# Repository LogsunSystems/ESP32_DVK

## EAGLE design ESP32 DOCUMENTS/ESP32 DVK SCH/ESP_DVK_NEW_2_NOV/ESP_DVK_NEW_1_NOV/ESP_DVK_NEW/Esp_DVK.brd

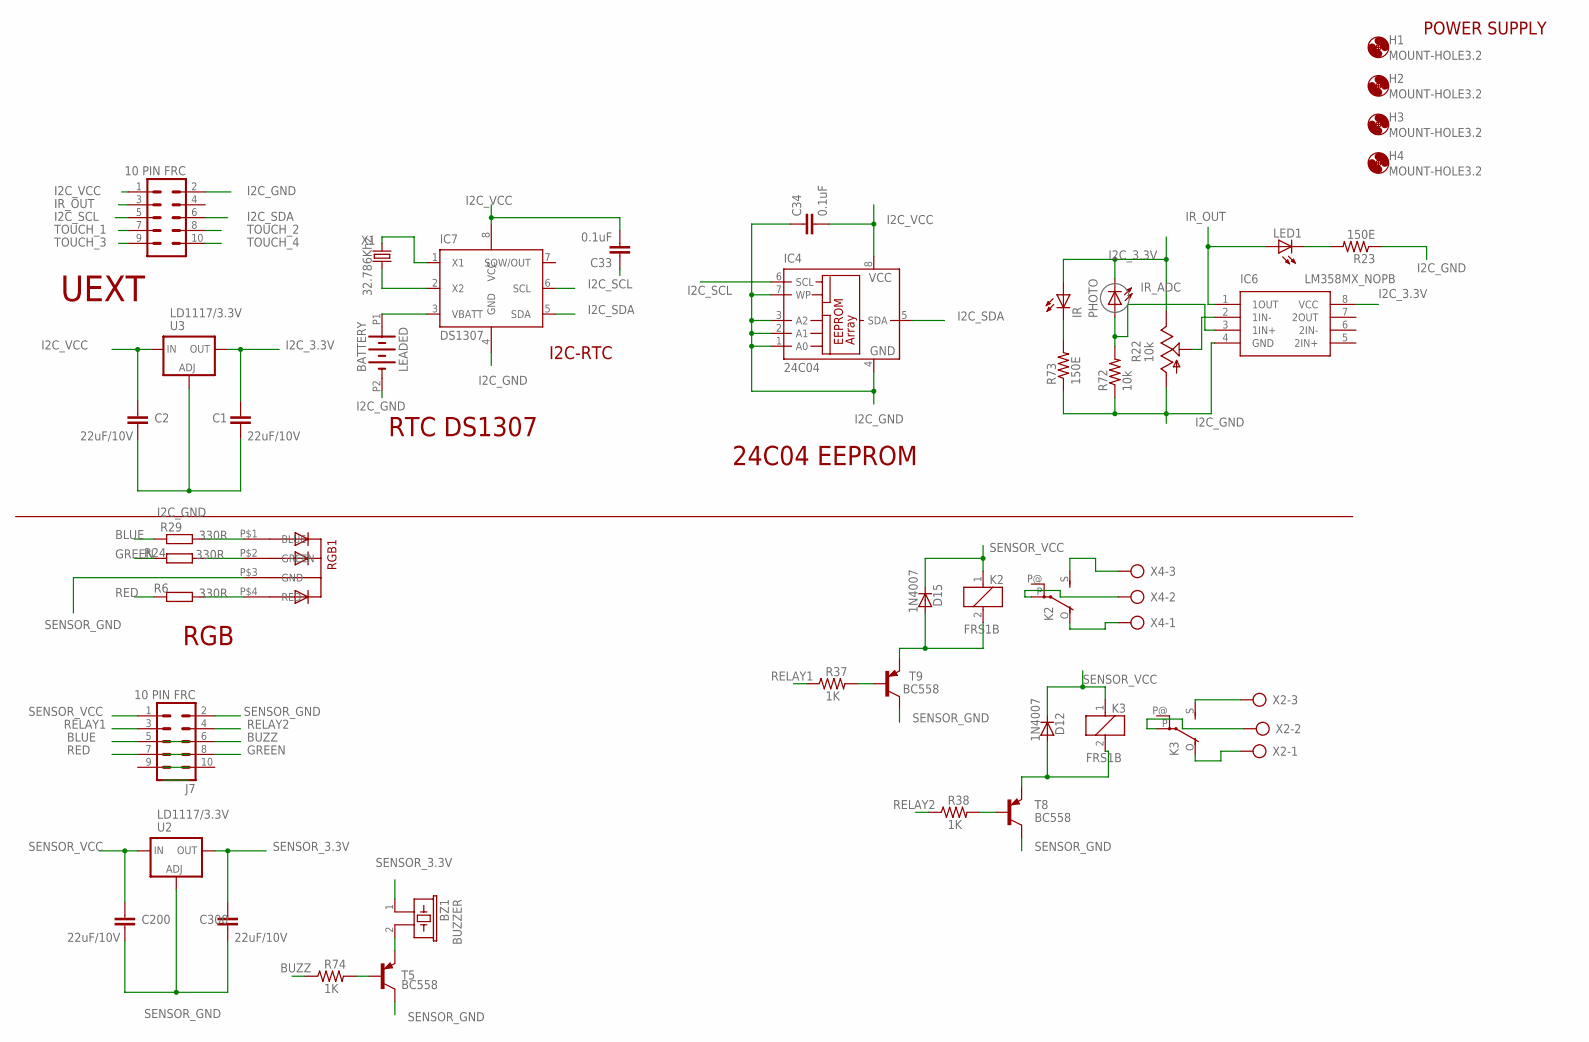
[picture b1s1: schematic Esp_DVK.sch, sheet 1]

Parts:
BATTERY: LEADED
BZ1: BUZZER; BUZZ
C1, C2, C200, C300: 22uF/10V; C1206
C33, C34: 0.1uF; C1206
D12, D15: 1N4007; MLL34
H1, H2, H3, H4: MOUNT-HOLE3.2; 3,2
IC4: 24C04; SO-08M
IC6: LM358MX_NOPB; SOIC127P600X175-8N
IC7: DS1307; SO08
IR: LED5MM
J3, J7: 10 PIN FRC; ML10
K2, K3: FRS1B
LED1: LEDCHIPLED_1206; CHIPLED_1206
PHOTO: LED5MM
R6, R24, R29: 330R; R1206
R22: 10k; RJ9W
R23, R73: 150E; R1206
R37, R38, R74: 1K; R1206@1
R72: 10k; R1206
RGB1: 5MMRGBLED; LED5MMRGB
T5, T8, T9: BC558; SOT23-EBC
U2, U3: LD1117/3.3V; SOT223
X1: 32.786Khz; TC38H
X2, X4: AK300/3

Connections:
BLUE: J7.5, R29.1
BUZZ: J7.6, R74.1
GREEN: J7.8, R24.1
I2C_3.3V: C1.2, IC6.8 (VCC), IR.A, PHOTO.K (C), R22.E, U3.4 (OUT)
I2C_GND: BATTERY.P2 (-), C1.1, C2.1, C33.1, C34.1, IC4.1 (A0), IC4.2 (A1), IC4.3 (A2), IC4.4 (GND), IC4.7 (WP), IC6.4 (GND), IC7.4 (GND), J3.2, R22.A, R23.1, R72.1, R73.1, U3.1 (ADJ)
I2C_SCL: IC4.6 (SCL), IC7.6 (SCL), J3.5
I2C_SDA: IC4.5 (SDA), IC7.5 (SDA), J3.6
I2C_VCC: C2.2, C33.2, C34.2, IC4.8 (VCC), IC7.8 (VCC), J3.1, U3.3 (IN)
IR_ADC: IC6.3 (1IN+), PHOTO.A, R72.2
IR_OUT: IC6.1 (1OUT), J3.3, LED1.A
unnamed: R24.2, RGB1.P$2 (GREEN)
unnamed: IC6.2 (1IN-), R22.S
unnamed: K3.S, X2.3
unnamed: K2.S, X4.3
unnamed: K2.P, X4.2
unnamed: R29.2, RGB1.P$1 (BLUE)
unnamed: K2.O, X4.1
unnamed: R38.2, T8.B
unnamed: IR.K (C), R73.2
unnamed: R6.2, RGB1.P$4 (RED)
unnamed: LED1.C, R23.2
unnamed: D12.A, K3.2, T8.E
unnamed: K3.P, X2.2
unnamed: K3.O, X2.1
unnamed: IC7.2 (X2), X1.1
unnamed: BATTERY.P1 (+), IC7.3 (VBATT)
unnamed: IC7.1 (X1), X1.2
unnamed: R74.2, T5.B
unnamed: BZ1.2, T5.E
unnamed: R37.2, T9.B
unnamed: D15.A, K2.2, T9.E
RED: J7.7, R6.1
RELAY1: J7.3, R37.1
RELAY2: J7.4, R38.1
SENSOR_3.3V: BZ1.1, C300.2, U2.4 (OUT)
SENSOR_GND: C200.1, C300.1, J7.2, RGB1.P$3 (GND), T5.C, T8.C, T9.C, U2.1 (ADJ)
SENSOR_VCC: C200.2, D12.C, D15.C, J7.1, K2.1, K3.1, U2.3 (IN)
SQW/OUT: IC7.7 (SQW/OUT)
TOUCH_1: J3.7
TOUCH_2: J3.8
TOUCH_3: J3.9
TOUCH_4: J3.10

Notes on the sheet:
POWER SUPPLY
I2C-RTC
RTC DS1307
24C04 EEPROM
UEXT
RGB

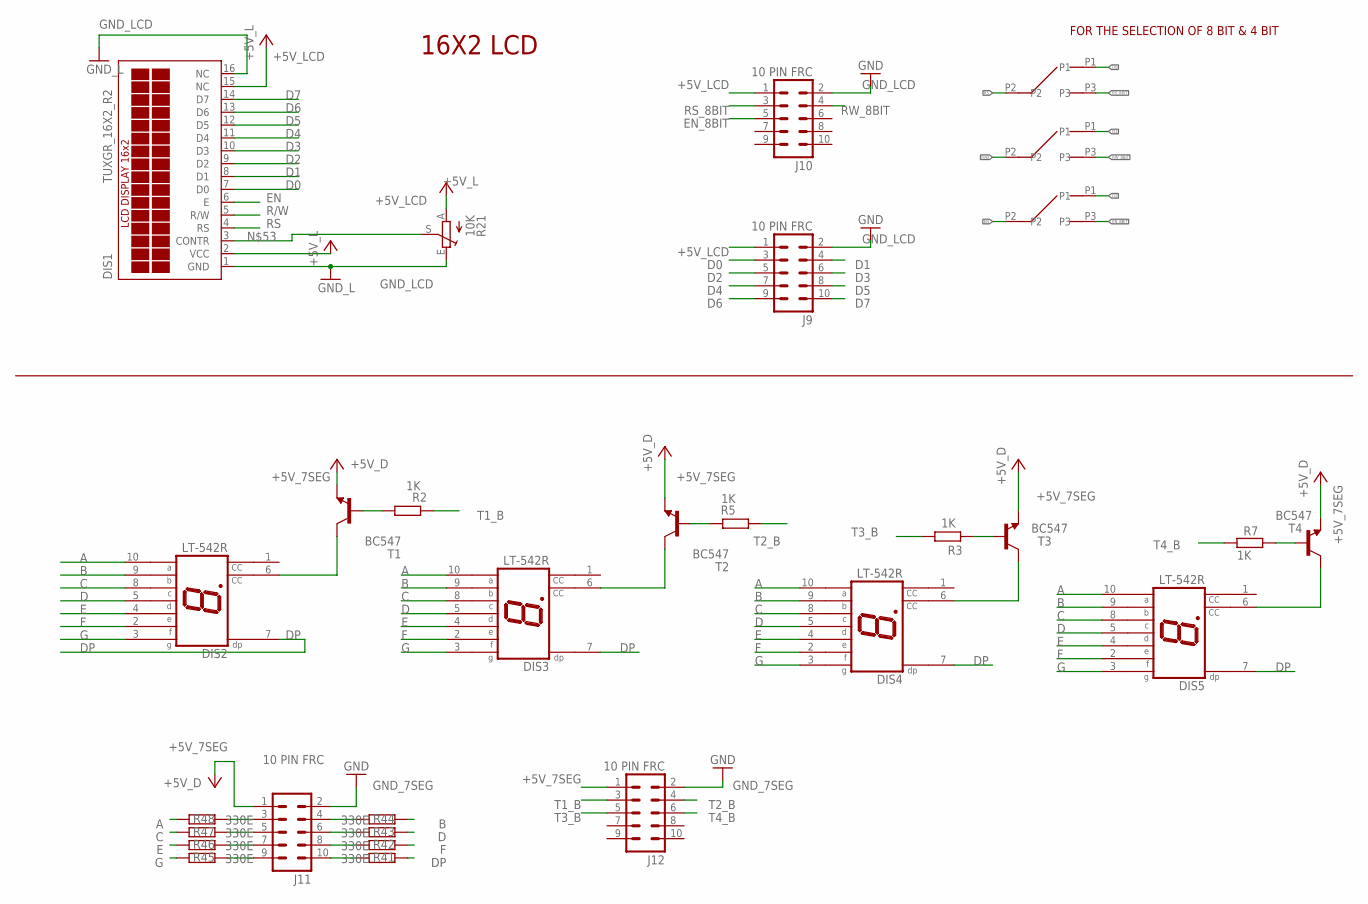
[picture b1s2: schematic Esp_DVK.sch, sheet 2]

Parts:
DIS1: TUXGR_16X2_R2
DIS2, DIS3, DIS4, DIS5: LT-542R; HDSP-A
EN: SMALLSLIDESW; SLIDESW
J9, J10, J11, J12: 10 PIN FRC; ML10
R2, R3, R5, R7: 1K; M1206
R21: 10K; RJ9W
R41, R42, R43, R44, R45, R46, R47, R48: 330E; R1206
R/W: SMALLSLIDESW; SLIDESW
RS: SMALLSLIDESW; SLIDESW
T1, T2, T3, T4: BC547; TO92

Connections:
+5V_7SEG: J11.1, J12.1, T1.1 (E), T2.1 (E), T3.1 (E), T4.1 (E)
+5V_LCD: DIS1.2 (VCC), DIS1.15 (NC), J9.1, J10.1, R21.A
A: DIS2.10 (A), DIS3.10 (A), DIS4.10 (A), DIS5.10 (A), R48.1
B: DIS2.9 (B), DIS3.9 (B), DIS4.9 (B), DIS5.9 (B), R44.2
C: DIS2.8 (C), DIS3.8 (C), DIS4.8 (C), DIS5.8 (C), R47.1
D: DIS2.5 (D), DIS3.5 (D), DIS4.5 (D), DIS5.5 (D), R43.2
D0: DIS1.7 (D0), J9.3, RS.P1
D1: DIS1.8 (D1), J9.4, R/W.P1
D2: DIS1.9 (D2), EN.P1, J9.5
D3: DIS1.10 (D3), J9.6
D4: DIS1.11 (D4), J9.7
D5: DIS1.12 (D5), J9.8
D6: DIS1.13 (D6), J9.9
D7: DIS1.14 (D7), J9.10
DP: DIS2.7 (DP), DIS3.7 (DP), DIS4.7 (DP), DIS5.7 (DP), R41.2
E: DIS2.4 (E), DIS3.4 (E), DIS4.4 (E), DIS5.4 (E), R46.1
EN: DIS1.6 (E), EN.P2
EN_8BIT: EN.P3, J10.5
F: DIS2.2 (F), DIS3.2 (F), DIS4.2 (F), DIS5.2 (F), R42.2
G: DIS2.3 (G), DIS3.3 (G), DIS4.3 (G), DIS5.3 (G), R45.1
GND_7SEG: J11.2, J12.2
GND_LCD: DIS1.1 (GND), DIS1.16 (NC), J9.2, J10.2, R21.E
unnamed: R3.1, T3.2 (B)
unnamed: R2.1, T1.2 (B)
unnamed: DIS2.6 (CC), T1.3 (C)
unnamed: DIS4.6 (CC), T3.3 (C)
unnamed: R5.1, T2.2 (B)
unnamed: DIS3.6 (CC), T2.3 (C)
unnamed: R7.1, T4.2 (B)
unnamed: DIS5.6 (CC), T4.3 (C)
unnamed: J11.4, R44.1
unnamed: J11.6, R43.1
unnamed: J11.8, R42.1
unnamed: J11.10, R41.1
unnamed: J11.3, R48.2
unnamed: J11.5, R47.2
unnamed: DIS1.3 (CONTR), R21.S
unnamed: J11.7, R46.2
unnamed: J11.9, R45.2
R/W: DIS1.5 (R/W), R/W.P2
RS: DIS1.4 (RS), RS.P2
RS_8BIT: J10.3, RS.P3
RW_8BIT: J10.4, R/W.P3
T1_B: J12.3, R2.2
T2_B: J12.4, R5.2
T3_B: J12.5, R3.2
T4_B: J12.6, R7.2

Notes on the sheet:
16X2 LCD
FOR THE SELECTION OF 8 BIT & 4 BIT

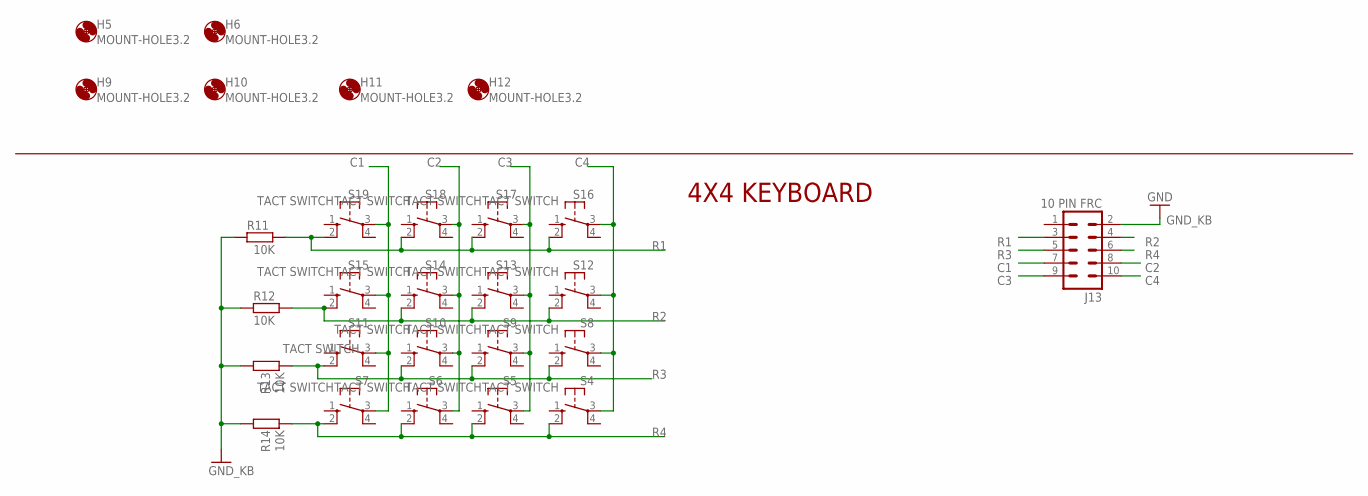
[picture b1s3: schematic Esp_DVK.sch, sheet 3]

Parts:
H5, H6, H9, H10, H11, H12: MOUNT-HOLE3.2; 3,2
J13: 10 PIN FRC; ML10
R11, R12, R13, R14: 10K; R1206
S4, S5, S6., S7, S8, S9, S10, S11, S12, S13, S14, S15, S16, S17, S18, S19: TACT SWITCH; B3F-10XX

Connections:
C1: J13.7, S7.3, S11.3, S15.3, S19.3
C2: J13.8, S6..3, S10.3, S14.3, S18.3
C3: J13.9, S5.3, S9.3, S13.3, S17.3
C4: J13.10, S4.3, S8.3, S12.3, S16.3
GND_KB: J13.2, R11.2, R12.2, R13.2, R14.2
R1: J13.3, R11.1, S16.2 (S1), S17.2 (S1), S18.2 (S1), S19.2 (S1)
R2: J13.4, R12.1, S12.2 (S1), S13.2 (S1), S14.2 (S1), S15.2 (S1)
R3: J13.5, R13.1, S8.2 (S1), S9.2 (S1), S10.2 (S1), S11.2 (S1)
R4: J13.6, R14.1, S4.2 (S1), S5.2 (S1), S6..2 (S1), S7.2 (S1)

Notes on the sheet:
4X4 KEYBOARD

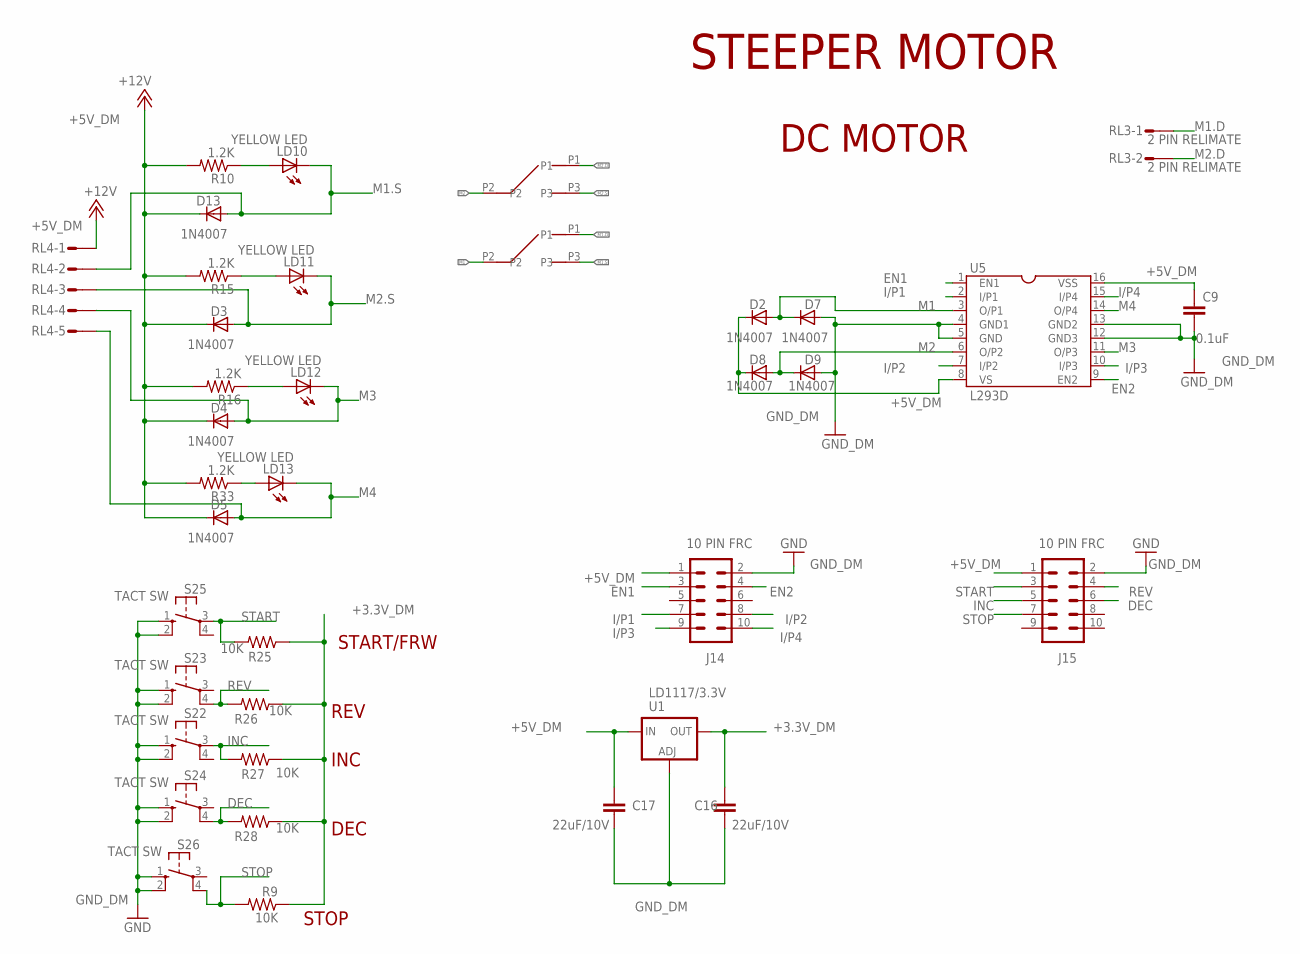
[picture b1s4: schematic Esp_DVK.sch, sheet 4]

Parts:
C9: 0.1uF; C1206
C16, C17: 22uF/10V; C1206
D2, D3, D4, D5, D7, D8, D9, D13: 1N4007; MLL34
J14, J15: 10 PIN FRC; ML10
LD10, LD11, LD12, LD13: YELLOW LED; CHIPLED_1206
R9, R25, R26, R27, R28: 10K; R1206@1
R10, R15, R16, R33: 1.2K; R1206@1
RL3: 2 PIN RELIMATE; S02P
RL4: S05P
S22, S23, S24, S25, S26: TACT SW; B3F-10XX
S_14, S_15: SMALLSLIDESW; SLIDESW
U1: LD1117/3.3V; SOT223
U5: L293D; SOCKET-16

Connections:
+3.3V_DM: C16.2, R9.1, R25.1, R26.1, R27.1, R28.1, U1.4 (OUT)
+5V_DM: C9.2, C17.2, D2.C, D3.C, D4.C, D5.C, D8.C, D13.C, J14.1, J15.1, R10.2, R15.2, R16.2, R33.2, RL4.1, U1.3 (IN), U5.8 (VS), U5.16 (VSS)
DEC: J15.6, R28.2, S24.4 (P1)
EN1: J14.3, U5.1 (EN1)
EN2: J14.4, U5.9 (EN2)
GND_DM: C9.1, C16.1, C17.1, D7.A, D9.A, J14.2, J15.2, S22.1 (S), S22.2 (S1), S23.1 (S), S23.2 (S1), S24.1 (S), S24.2 (S1), S25.1 (S), S25.2 (S1), S26.1 (S), S26.2 (S1), U1.1 (ADJ), U5.4 (GND1), U5.5 (GND), U5.12 (GND3), U5.13 (GND2)
I/P1: J14.7, U5.2 (I/P1)
I/P2: J14.8, U5.7 (I/P2)
I/P3: J14.9, U5.10 (I/P3)
I/P4: J14.10, U5.15 (I/P4)
INC: J15.5, R27.2, S22.3
M1: D2.A, D7.C, S_15.P2, U5.3 (O/P1)
M1.D: RL3.1, S_15.P1
M1.S: D13.A, LD10.C, RL4.2, S_15.P3
M2: D8.A, D9.C, S_14.P2, U5.6 (O/P2)
M2.D: RL3.2, S_14.P1
M2.S: D3.A, LD11.C, RL4.3, S_14.P3
M3: D4.A, LD12.C, RL4.4, U5.11 (O/P3)
M4: D5.A, LD13.C, RL4.5, U5.14 (O/P4)
unnamed: LD10.A, R10.1
unnamed: LD11.A, R15.1
unnamed: LD12.A, R16.1
unnamed: LD13.A, R33.1
REV: J15.4, R26.2, S23.4 (P1)
START: J15.3, R25.2, S25.3
STOP: J15.7, R9.2, S26.4 (P1)

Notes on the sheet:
DC MOTOR
START/FRW
REV
INC
DEC
STOP
STEEPER MOTOR

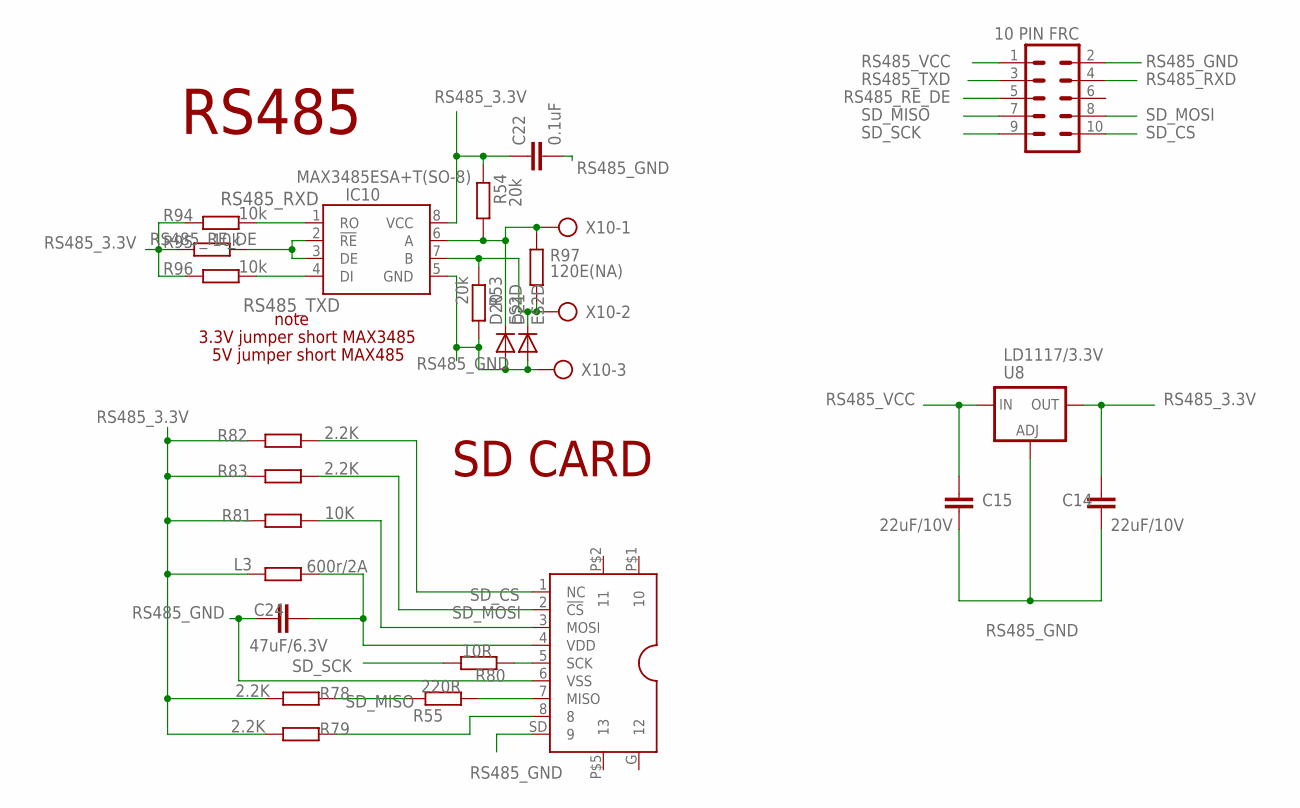
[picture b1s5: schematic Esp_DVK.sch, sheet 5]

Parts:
C14, C15: 22uF/10V; C1206
C22: 0.1uF; C0805
C24: 47uF/6.3V; C1206
D20, D21: ES2D; SMB
IC10: MAX3485ESA+T(SO-8); SOIC8
J5: 10 PIN FRC; ML10
L3: 600r/2A; R1206
R53, R54: 20k; R1206
R55: 220R; R1206
R78, R79, R82, R83: 2.2K; R1206
R80: 10R; R1206
R81: 10K; R1206
R94, R95, R96: 10k; R1206
R97: 120E(NA); R1206
U8: LD1117/3.3V; SOT223
X5: SDCARD-TF07; SDCARD
X10: AK300/3

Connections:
unnamed: D21.C, IC10.7 (B), R53.1, R97.2, X10.2
unnamed: D20.C, IC10.6 (A), R54.2, R97.1, X10.1
unnamed: R82.1, X5.1 (NC)
unnamed: C24.2, L3.1, X5.4 (VDD)
unnamed: R80.1, X5.5 (SCK)
unnamed: R55.1, X5.7 (MISO)
unnamed: R79.1, X5.8
RS485_3.3V: C14.2, C22.1, IC10.8 (VCC), L3.2, R54.1, R78.2, R79.2, R81.2, R82.2, R83.2, R94.1, R95.1, R96.1, U8.4 (OUT)
RS485_GND: C14.1, C15.1, C22.2, C24.1, D20.A, D21.A, IC10.5 (GND), J5.2, R53.2, U8.1 (ADJ), X5.6 (VSS), X5.SD (9), X10.3
RS485_RE_DE: IC10.2 (!RE), IC10.3 (DE), J5.5, R95.2
RS485_RXD: IC10.1 (RO), J5.4, R94.2
RS485_TXD: IC10.4 (DI), J5.3, R96.2
RS485_VCC: C15.2, J5.1, U8.3 (IN)
SD_CS: J5.10, R83.1, X5.2 (!CS)
SD_MISO: J5.7, R55.2, R78.1
SD_MOSI: J5.8, R81.1, X5.3 (MOSI)
SD_SCK: J5.9, R80.2

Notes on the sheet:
RS485
SD CARD
note
3.3V jumper short MAX3485
5V jumper short MAX485

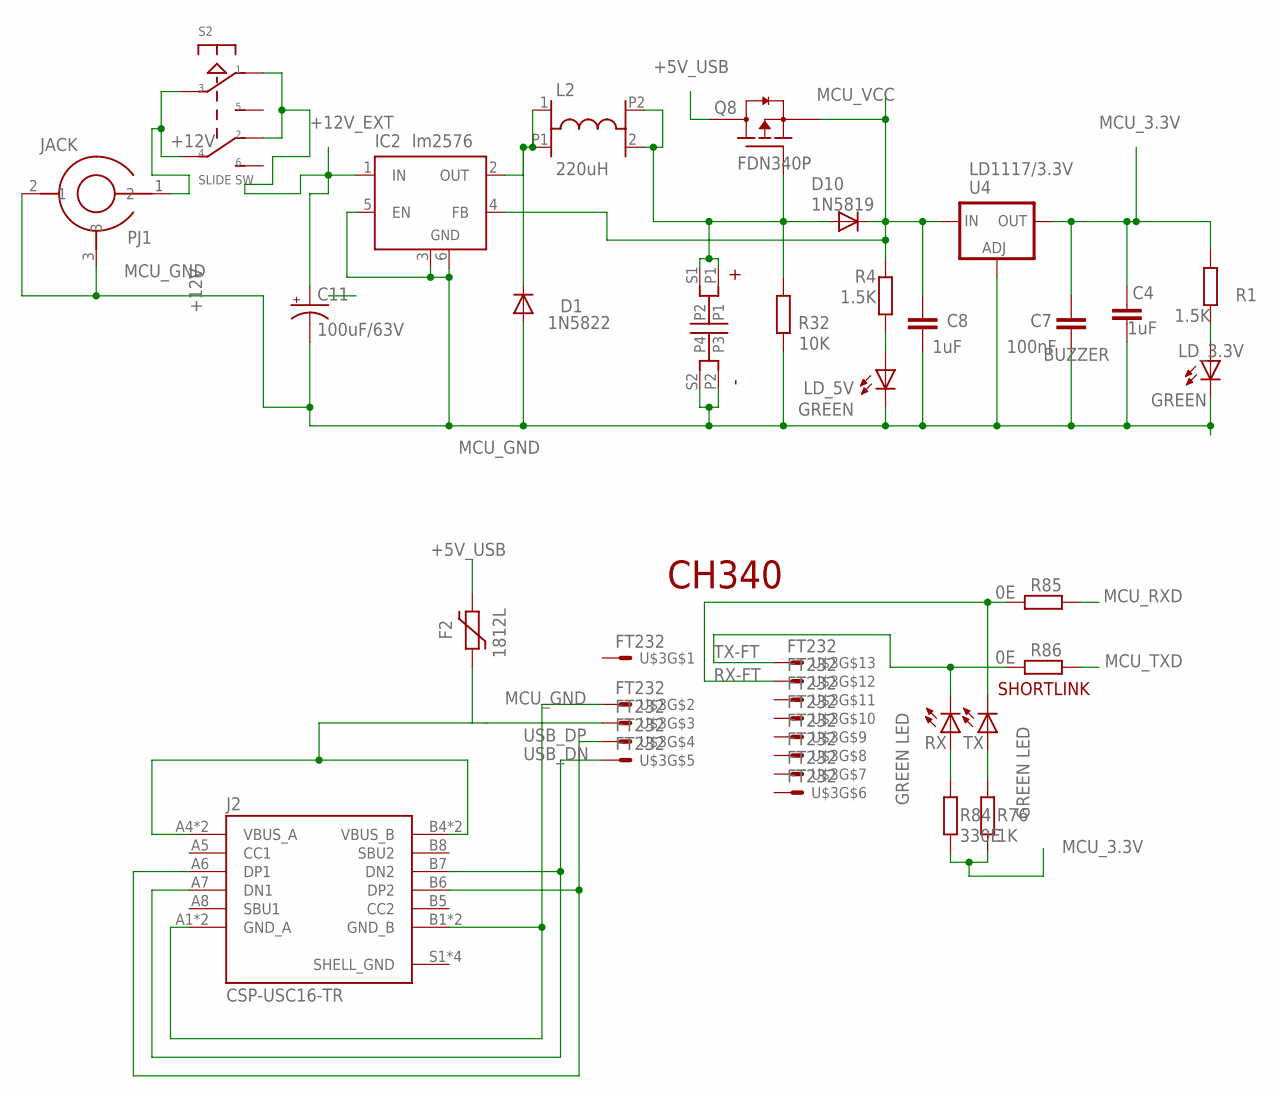
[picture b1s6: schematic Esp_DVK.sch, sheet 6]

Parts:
C4, C8: 1uF; C1206
C7: 100nF; C1206
C11: 100uF/63V; E3,5-10
C21: 1000uF/63V; 140CLH-1010
D1: 1N5822; DO201-15
D10: 1N5819; DO41-10
F2: 1812L
IC2: lm2576; TO263-5
J2: CSP-USC16-TR; VALCON_CSP-USC16-TR
L2: 220uH; MS42
LD_3.3V, LD_5V: GREEN; LED3MM
PJ1: JACK
Q8: FDN340P; SOT95P280X135-3N
R1, R4: 1.5K; R1206
R32: 10K; R1206
R76: 1K; R1206
R84: 330E; R1206
R85, R86: 0E; R1206
RX: GREEN LED; CHIPLED_1206
S2: SLIDE SW; SLIDE
TX: GREEN LED; CHIPLED_1206
U4: LD1117/3.3V; SOT223
U$3: FT232

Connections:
+5V_USB: F2.P$2 (2), Q8.3 (D)
+12V: PJ1.1 (2), S2.3, S2.4
+12V_EXT: C11.+, IC2.1 (IN), S2.1, S2.2
MCU_3.3V: C4.2, C7.2, R1.2, R76.1, R84.1, U4.4 (OUT); also elsewhere on the board
MCU_GND: C4.1, C7.1, C8.1, C11.-, C21.P2 (P3), C21.S2 (P4), D1.A, IC2.3 (GND), IC2.5 (EN), IC2.6 (GND), J2.A1 (GND_A), J2.A12 (GND_A), J2.B1 (GND_B), J2.B12 (GND_B), LD_3.3V.K (C), LD_5V.K (C), PJ1.2 (1), PJ1.3, R32.1, U4.1 (ADJ), U$3.2; also elsewhere on the board
MCU_RXD: R85.2; also elsewhere on the board
MCU_TXD: R86.2; also elsewhere on the board
MCU_VCC: C8.2, D10.C, IC2.4 (FB), Q8.2 (S), R4.2, U4.3 (IN); also elsewhere on the board
unnamed: D1.C, IC2.2 (OUT), L2.1, L2.P1 (2)
unnamed: F2.P$1 (1), J2.A4 (VBUS_A), J2.A9 (VBUS_A), J2.B4 (VBUS_B), J2.B9 (VBUS_B), U$3.3
unnamed: LD_5V.A, R4.1
unnamed: C21.P1, C21.S1 (P2), D10.A, L2.2 (3), L2.P2 (4), Q8.1 (G), R32.2
unnamed: LD_3.3V.A, R1.1
unnamed: R76.2, TX.A
unnamed: R84.2, RX.A
RX-FT: R85.1, TX.C, U$3.12
SHELL_GND: J2.S1 (SHELL_GND), J2.S2 (SHELL_GND), J2.S3 (SHELL_GND), J2.S4 (SHELL_GND)
TX-FT: R86.1, RX.C, U$3.13
USB_DN: J2.A7 (DN1), J2.B7 (DN2), U$3.5
USB_DP: J2.A6 (DP1), J2.B6 (DP2), U$3.4

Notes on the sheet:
BUZZER
CH340
SHORTLINK

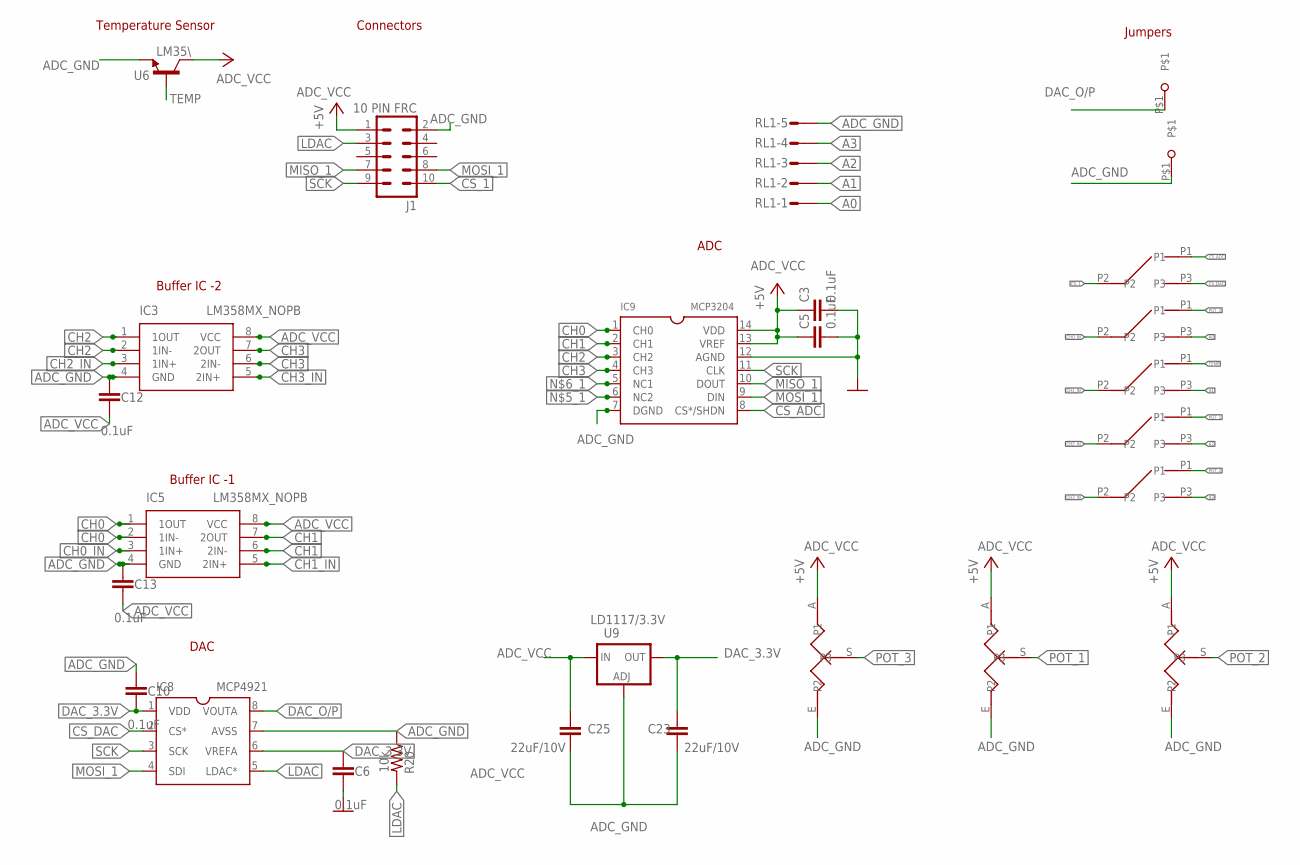
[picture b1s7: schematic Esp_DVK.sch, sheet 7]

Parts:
C3, C5, C6, C10, C12, C13: 0.1uF; C1206
C23, C25: 22uF/10V; C1206
DACO/P: TEST_PAD; 3.2MM
GND: TEST_PAD; 3.2MM
IC3, IC5: LM358MX_NOPB; SOIC127P600X175-8N
IC8: MCP4921; SOIC-8N
IC9: MCP3204; SOIC-14N
J1: 10 PIN FRC; ML10
POT1, POT2, POT3: 10K; CA6V
R20: 10k; R1206@1
RL1: S05P
S_9, S_10, S_11, S_12, S_13: SMALLSLIDESW; SLIDESW
U6: LM35\; TO92
U9: LD1117/3.3V; SOT223

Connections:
A0: RL1.1, S_10.P3
A1: RL1.2, S_11.P3
A2: RL1.3, S_12.P3
A3: RL1.4, S_13.P3
ADC_GND: C10.1, C12.1, C13.1, C23.1, C25.1, GND.P$1, IC3.4 (GND), IC5.4 (GND), IC8.7 (AVSS), IC9.7 (DGND), J1.2, POT1.E (P2), POT2.E (P2), POT3.E (P2), R20.1, RL1.5, U6.1 (E), U9.1 (ADJ)
ADC_VCC: C3.1, C5.1, C12.2, C13.2, C25.2, IC3.8 (VCC), IC5.8 (VCC), IC9.13 (VREF), IC9.14 (VDD), J1.1, POT1.A (P1), POT2.A (P1), POT3.A (P1), U6.3 (C), U9.3 (IN)
CH0: IC5.1 (1OUT), IC5.2 (1IN-), IC9.1 (CH0)
CH0_IN: IC5.3 (1IN+), S_10.P2
CH1: IC5.6 (2IN-), IC5.7 (2OUT), IC9.2 (CH1)
CH1_IN: IC5.5 (2IN+), S_11.P2
CH2: IC3.1 (1OUT), IC3.2 (1IN-), IC9.3 (CH2)
CH2_IN: IC3.3 (1IN+), S_12.P2
CH3: IC3.6 (2IN-), IC3.7 (2OUT), IC9.4 (CH3)
CH3_IN: IC3.5 (2IN+), S_13.P2
CS_1: J1.10, S_9.P2
CS_ADC: IC9.8 (CS*/SHDN), S_9.P1
CS_DAC: IC8.2 (CS*), S_9.P3
DAC_3.3V: C6.1, C10.2, C23.2, IC8.1 (VDD), IC8.6 (VREFA), U9.4 (OUT)
DAC_O/P: DACO/P.P$1, IC8.8 (VOUTA)
GND_ADC: C3.2, C5.2, C6.2, IC9.12 (AGND)
LDAC: IC8.5 (LDAC*), J1.3, R20.2
MISO_1: IC9.10 (DOUT), J1.7
MOSI_1: IC8.4 (SDI), IC9.9 (DIN), J1.8
POT_1: POT3.S (P3), S_12.P1
POT_2: POT2.S (P3), S_13.P1
POT_3: POT1.S (P3), S_10.P1
SCK: IC8.3 (SCK), IC9.11 (CLK), J1.9
TEMP: S_11.P1, U6.2 (B)

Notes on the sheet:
Temperature Sensor
Connectors
ADC
DAC
Jumpers
Buffer IC -1
Buffer IC -2

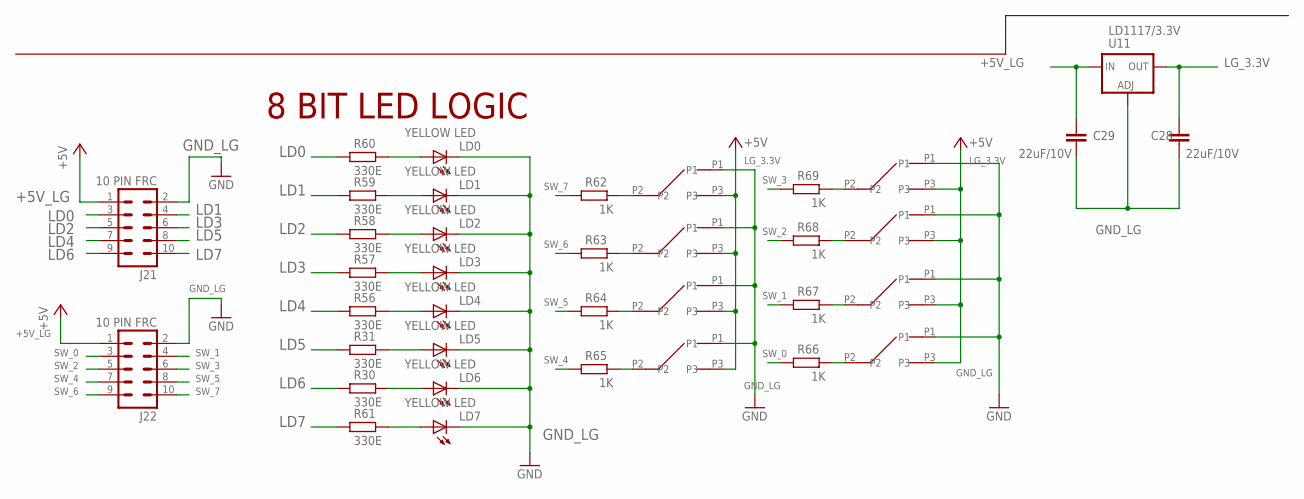
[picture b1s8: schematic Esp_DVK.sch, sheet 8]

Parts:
C28, C29: 22uF/10V; C1206
J21, J22: 10 PIN FRC; ML10
L4, L5, L6, L7, L8, L9, L10, L11: YELLOW LED; CHIPLED_1206
R30, R31, R56, R57, R58, R59, R60, R61: 330E; R1206
R62, R63, R64, R65, R66, R67, R68, R69: 1K; R1206
S_1, S_2, S_3, S_4, S_5, S_6, S_7, S_8: SMALLSLIDESW; SLIDESW
U11: LD1117/3.3V; SOT223

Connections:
+5V_LG: C29.2, J21.1, J22.1, U11.3 (IN)
GND_LG: C28.1, C29.1, J21.2, J22.2, L4.C, L5.C, L6.C, L7.C, L8.C, L9.C, L10.C, L11.C, S_1.P1, S_2.P1, S_3.P1, S_4.P1, S_5.P1, S_6.P1, S_7.P1, S_8.P1, U11.1 (ADJ)
LD0: J21.3, R60.1
LD1: J21.4, R59.1
LD2: J21.5, R58.1
LD3: J21.6, R57.1
LD4: J21.7, R56.1
LD5: J21.8, R31.1
LD6: J21.9, R30.1
LD7: J21.10, R61.1
LG_3.3V: C28.2, S_1.P3, S_2.P3, S_3.P3, S_4.P3, S_5.P3, S_6.P3, S_7.P3, S_8.P3, U11.4 (OUT)
unnamed: L4.A, R60.2
unnamed: L5.A, R59.2
unnamed: R62.2, S_8.P2
unnamed: L6.A, R58.2
unnamed: L7.A, R57.2
unnamed: L8.A, R56.2
unnamed: L9.A, R31.2
unnamed: L10.A, R30.2
unnamed: L11.A, R61.2
unnamed: R63.2, S_7.P2
unnamed: R64.2, S_6.P2
unnamed: R65.2, S_5.P2
unnamed: R69.2, S_4.P2
unnamed: R68.2, S_3.P2
unnamed: R67.2, S_2.P2
unnamed: R66.2, S_1.P2
SW_0: J22.3, R66.1
SW_1: J22.4, R67.1
SW_2: J22.5, R68.1
SW_3: J22.6, R69.1
SW_4: J22.7, R65.1
SW_5: J22.8, R64.1
SW_6: J22.9, R63.1
SW_7: J22.10, R62.1

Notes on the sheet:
8 BIT LED LOGIC

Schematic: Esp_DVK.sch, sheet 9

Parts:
C20: 0.1uF; C1206
D18: IN5819/SOD123; SOD123
GP1, GP2, GP3: ML10
J4: 22-27-2071-07; 6410-07
POT4: 10K; CA6V
R8, R17: 2.2K; R1206
R18, R91: 10K; R1206
R40: 470K; R1206
R75: NA; R1206
RESET: 10-XX; B3F-10XX
U$4: ESP32
UEXT: ML10

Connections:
ESP_EN: C20.1, R40.1, RESET.1 (S), RESET.2 (S1), U$4.EN
IO0: R75.2, U$4.GPIO0
IO2: GP1.5, U$4.GPIO2
IO4: GP1.6, U$4.GPIO4
IO6: U$4.GPIO6
IO7: U$4.GPIO7
IO8: U$4.GPIO8
IO9: U$4.GPIO9
IO10: U$4.GPIO10
IO11: U$4.GPIO11
IO12: GP1.8, U$4.GPIO12
IO13: GP1.7, U$4.GPIO13
IO14: GP1.9, U$4.GPIO14
IO15: GP1.4, U$4.GPIO15
IO16: D18.A, GP2.4, R91.2, U$4.GPIO16
IO17: GP2.3, U$4.GPIO17, UEXT.3
IO25: GP3.9, U$4.GPIO25
IO26: GP3.10, U$4.GPIO26
IO27: GP1.10, U$4.GPIO27
IO32: GP3.7, U$4.GPIO32
IO33: GP3.8, U$4.GPIO33
IO34: GP3.5, J4.5, U$4.GPIO34
IO35: GP3.6, J4.6, U$4.GPIO35
IO36: GP3.3, J4.3, U$4.GPIO36
IO39: GP3.4, J4.4, U$4.GPIO39
MCU_3.3V: J4.1, POT4.A (P1), R8.1, R17.1, R18.1, R40.2, R75.1, R91.1, U$4.3.3V; also elsewhere on the board
MCU_CS: GP2.10, R18.2, U$4.GPIO5, UEXT.10
MCU_GND: C20.2, GP1.2, GP2.2, GP3.2, J4.7, POT4.E (P2), RESET.3, RESET.4 (P1), U$4.GND1, U$4.GND2, U$4.GND3, UEXT.2; also elsewhere on the board
MCU_MISO: GP2.7, U$4.GPIO19, UEXT.7
MCU_MOSI: GP2.8, U$4.GPIO23, UEXT.8
MCU_RXD: U$4.RX; also elsewhere on the board
MCU_SCK: GP2.9, U$4.GPIO18, UEXT.9
MCU_SCL: GP2.5, R8.2, U$4.GPIO22, UEXT.5
MCU_SDA: GP2.6, R17.2, U$4.GPIO21, UEXT.6
MCU_TXD: GP1.3, U$4.TX; also elsewhere on the board
MCU_VCC: GP1.1, GP2.1, GP3.1, U$4.5V, UEXT.1; also elsewhere on the board
unnamed: D18.C, UEXT.4
POT: J4.2, POT4.S (P3)

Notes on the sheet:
RESET
UEXT
relement connector

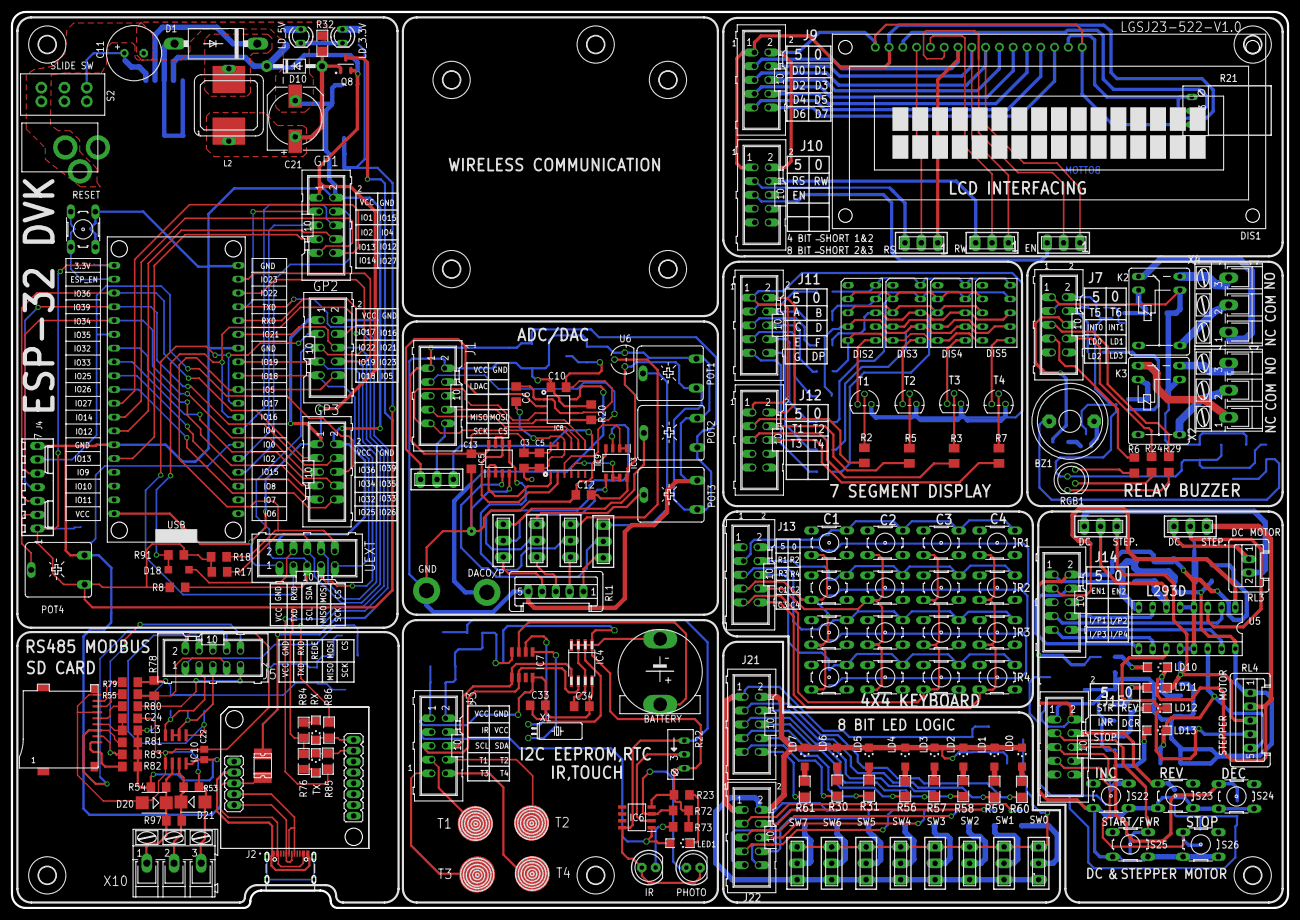
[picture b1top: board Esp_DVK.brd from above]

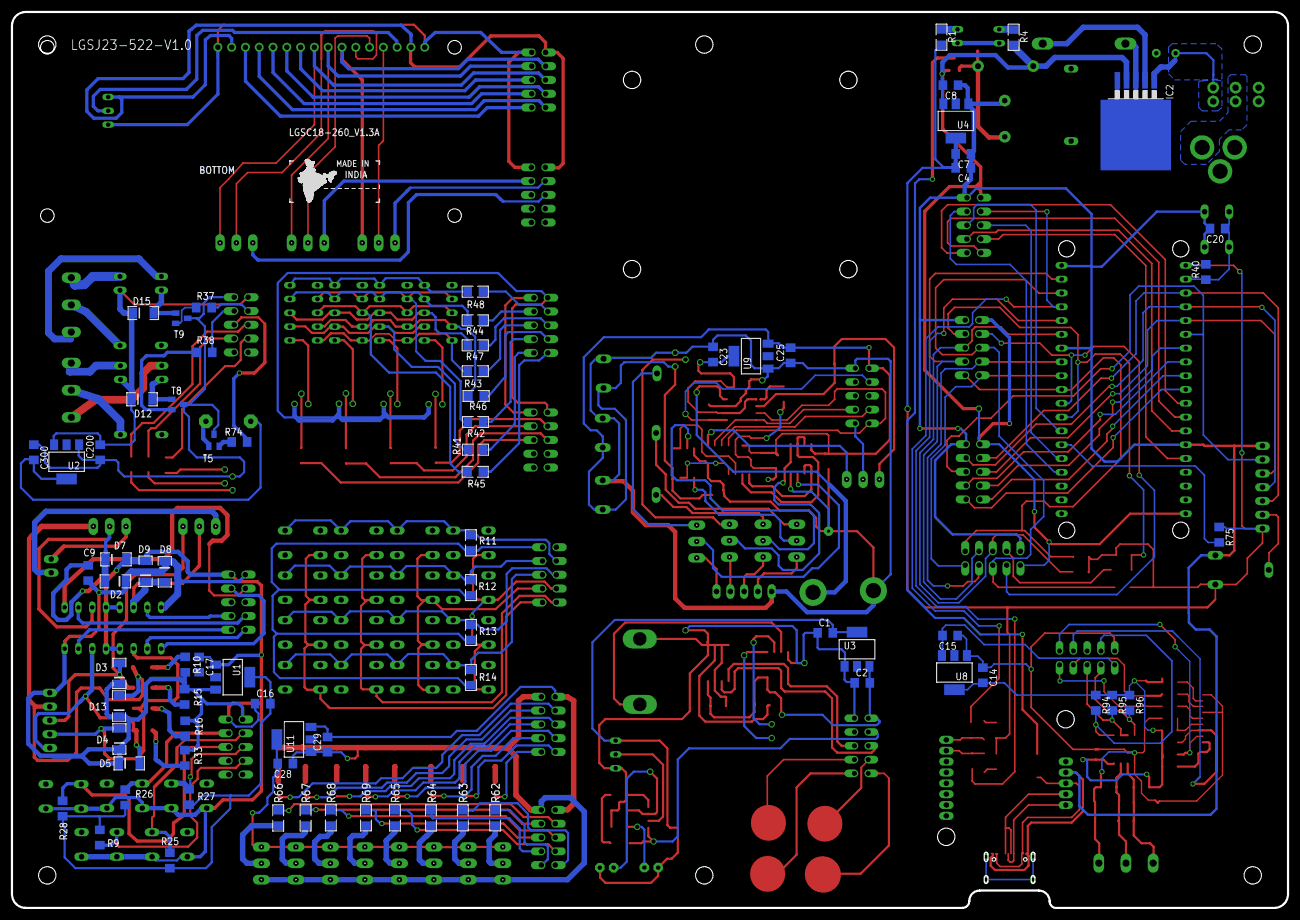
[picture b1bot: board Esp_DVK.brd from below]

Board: 2 copper layers, 235.0 x 165.0 mm, 269 parts (78 on the bottom side), 246 nets.

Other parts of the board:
U$1: MAD_IN_INDIA

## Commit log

2023-11-11 ESP32 DVK
2023-11-11 Sample Codes added
